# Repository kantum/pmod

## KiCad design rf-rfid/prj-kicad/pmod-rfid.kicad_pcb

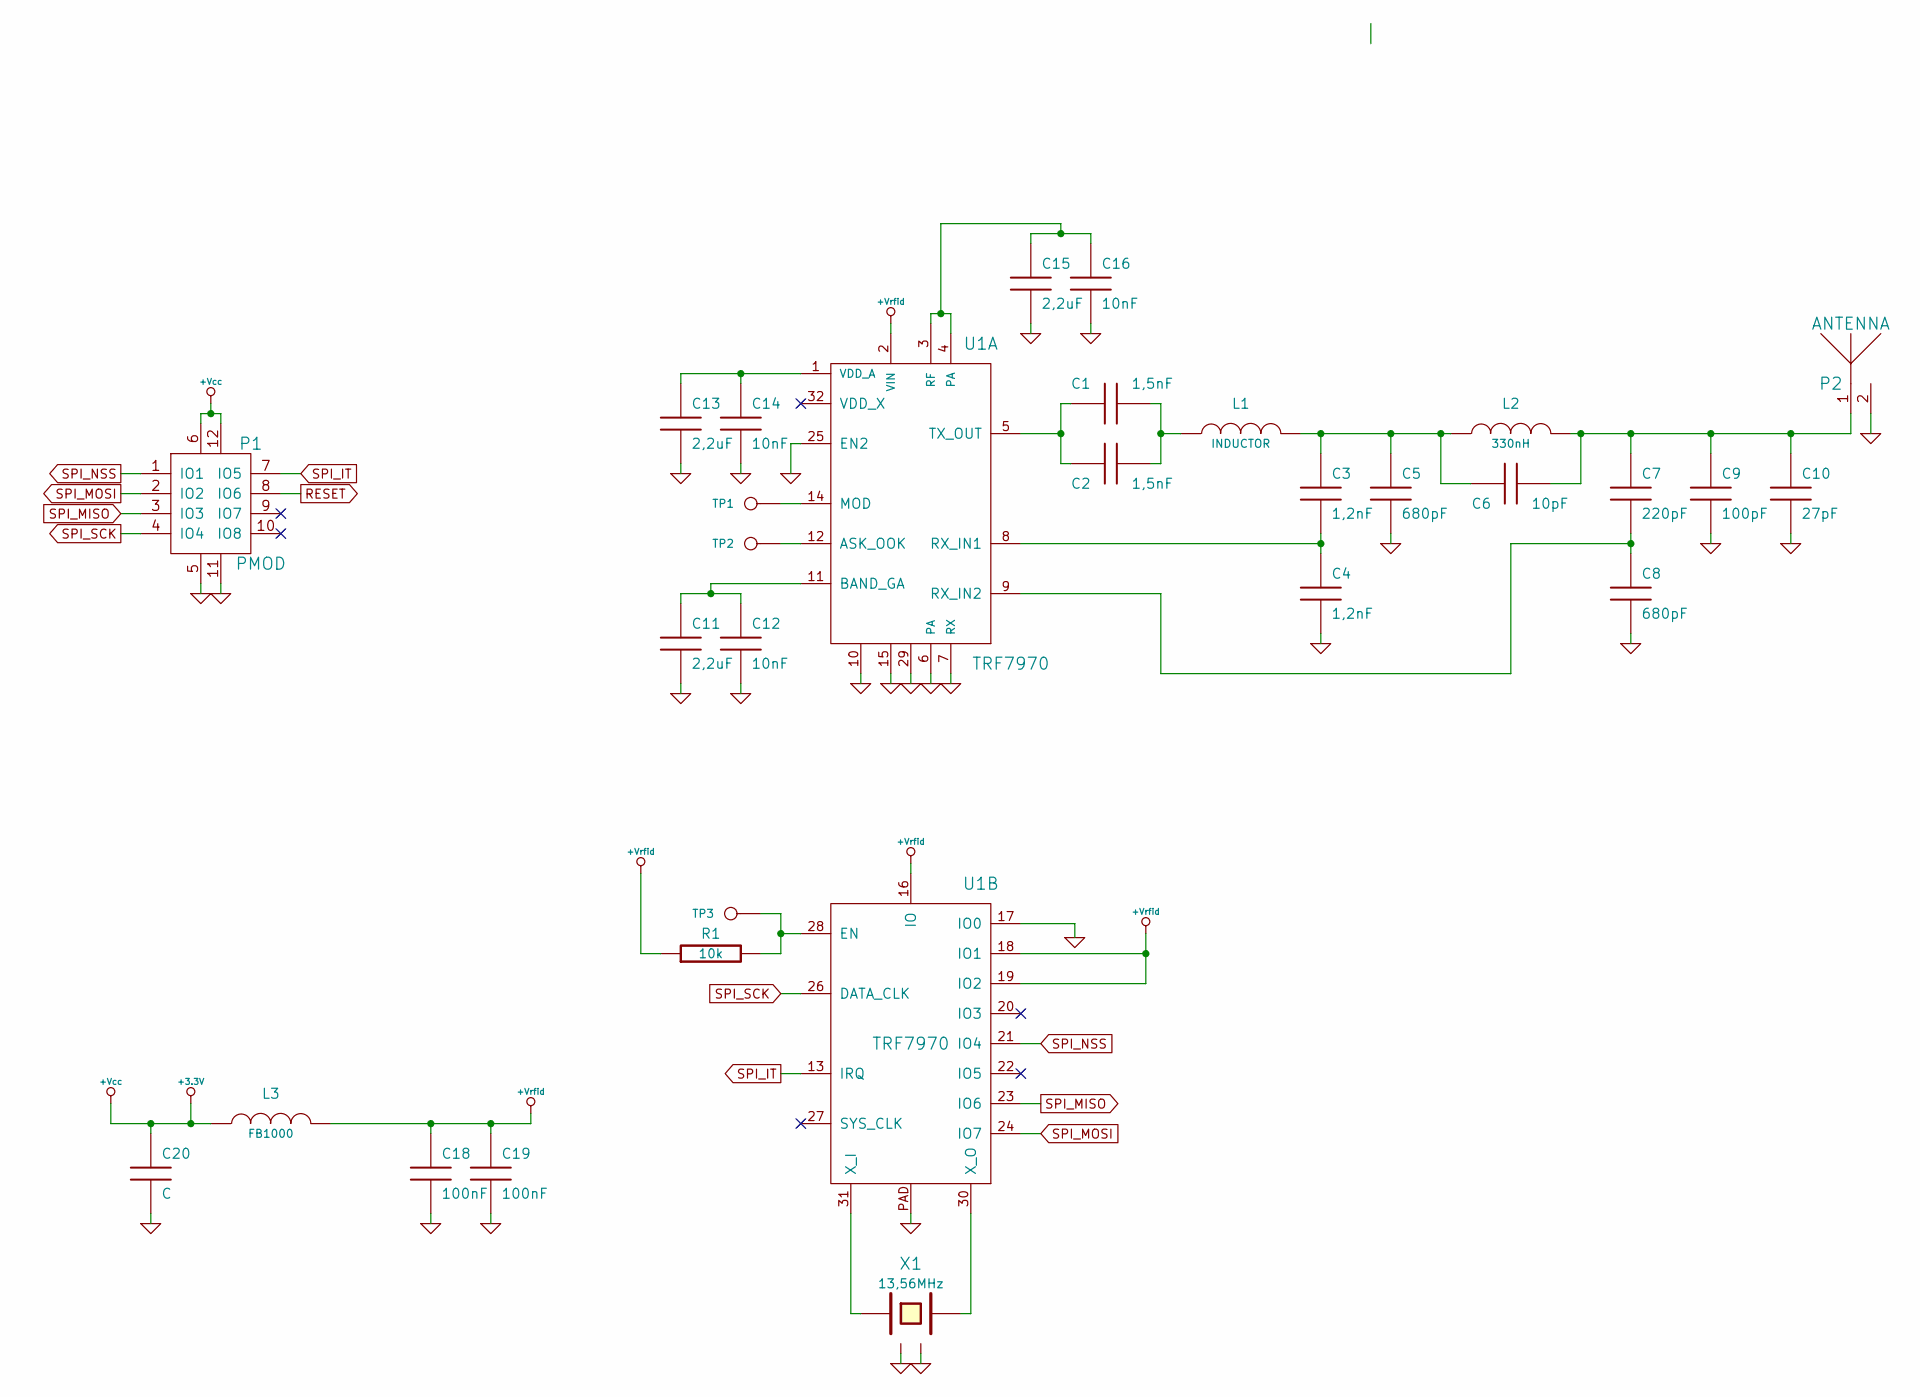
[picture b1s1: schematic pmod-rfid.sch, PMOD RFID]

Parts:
C1, C2: 1,5nF; SMD0603
C3, C4: 1,2nF; SMD0603
C5, C8: 680pF; SMD0603
C6: 10pF; SMD0603
C7: 220pF; SMD0603
C9: 100pF; SMD0603
C10: 27pF; SMD0603
C11, C13, C15: 2,2uF; SMD0603
C12, C14, C16: 10nF; SMD0603
C18, C19: 100nF; SMD0603
C20: C; SMD0805
L1: INDUCTOR; I_1008CS
L2: 330nH; I_1008CS
L3: FB1000; SMD0603
P1: PMOD; CONN_PMOD-Male
P2: ANTENNA; CONN_SMA_RA
R1: 10k; SMD0603
TP1, TP2, TP3: CONN_1; TP_SMD
U1: TRF7970; QFN32
X1: 13,56MHz; Q_SMD5x3

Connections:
+3.3V: C20.1, L3.1, P1.6, P1.12
+Vrfid: C18.1, C19.1, L3.2, R1.1, U1.2 (VIN), U1.16 (IO), U1.18 (IO1), U1.19 (IO2)
GND: C4.2, C5.2, C8.2, C9.2, C10.2, C11.2, C12.2, C13.2, C14.2, C15.2, C16.2, C18.2, C19.2, C20.2, P1.5, P1.11, P2.2, U1.6 (PA), U1.7 (RX), U1.10, U1.15, U1.17 (IO0), U1.25 (EN2), U1.29, U1.PAD, X1.2, X1.4
unnamed: C1.1, C2.1, L1.1
unnamed: C1.2, C2.2, U1.5 (TX_OUT)
unnamed: C3.1, C5.1, C6.2, L1.2, L2.1
unnamed: C3.2, C4.1, U1.8 (RX_IN1)
unnamed: C7.2, C8.1, U1.9 (RX_IN2)
unnamed: C6.1, C7.1, C9.1, C10.1, L2.2, P2.1
unnamed: C11.1, C12.1, U1.11 (BAND_GA)
unnamed: C13.1, C14.1, U1.1 (VDD_A)
unnamed: C15.1, C16.1, U1.3 (RF), U1.4 (PA)
unnamed: R1.2, TP3.1, U1.28 (EN)
unnamed: TP1.1, U1.14 (MOD)
unnamed: TP2.1, U1.12 (ASK_OOK)
unnamed: U1.30 (X_O), X1.3
unnamed: U1.31 (X_I), X1.1
RESET: P1.8 (IO6)
SPI_IT: P1.7 (IO5), U1.13 (IRQ)
SPI_MISO: P1.3 (IO3), U1.23 (IO6)
SPI_MOSI: P1.2 (IO2), U1.24 (IO7)
SPI_NSS: P1.1 (IO1), U1.21 (IO4)
SPI_SCK: P1.4 (IO4), U1.26 (DATA_CLK)

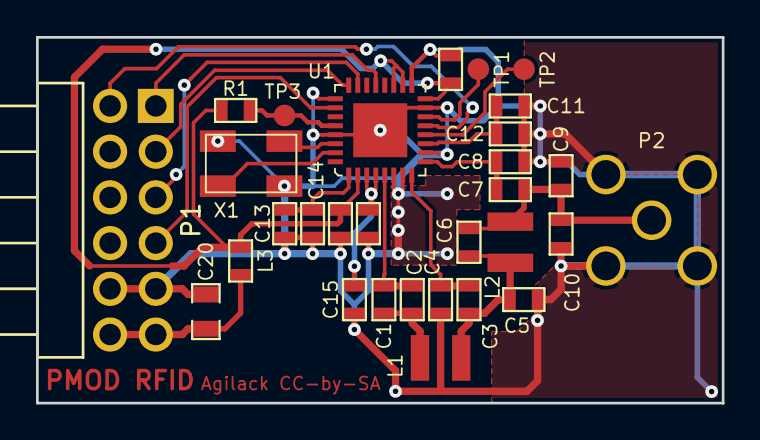
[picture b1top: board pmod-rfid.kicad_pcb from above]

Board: 2 copper layers, 38.1 x 20.3 mm, 30 parts (0 on the bottom side), 22 nets.

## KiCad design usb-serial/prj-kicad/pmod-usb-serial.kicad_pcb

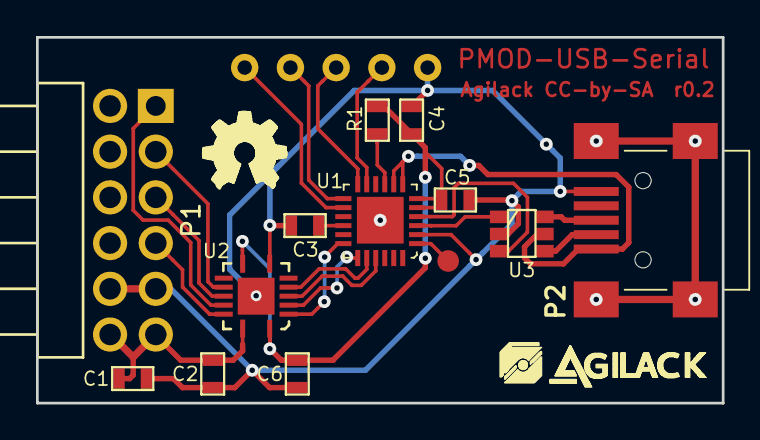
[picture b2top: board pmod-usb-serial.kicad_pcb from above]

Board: 2 copper layers, 38.1 x 20.3 mm, 20 parts (0 on the bottom side), 23 nets.

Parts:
C1, C4: 1uF; SMD0603
C2, C5, C6: 100nF; SMD0603
C3: 4,7uF; SMD0603
P1: PMOD; CONN_PMOD-Male
P2: CONN_MiniUSB-AB; CONN_65100516121
R1: 4,7k; SMD0603
TP1, TP2, TP3, TP4, TP5: CONN_1; TP_PIN
TP6: CONN_1; TP_SMD
U1: CP2104; QFN24
U2: TXS0104; QFN14
U3: USBLC6-2; SOT23-6
agilack-11.5: 450px; logo-agilack-11.5
logo_ohw: VAL**; logo-ohw

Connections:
CP21_CTS: U1.18, U2.2
CP21_RTS: U1.19, U2.3
CP21_RXD: U1.20, U2.5
CP21_TXD: U1.21, U2.4
GND: C1.2, C2.2, C3.2, C4.2, C5.2, C6.2, P1.5, P1.11, P2.5, TP5.1, U1.2, U1.PAD, U2.7, U2.PAD, U3.2
unnamed: C3.1, U1.16
unnamed: P2.1, U1.7, U1.8, U3.5
unnamed: P2.2, U3.4
unnamed: P2.3, U3.6
unnamed: TP1.1, U1.14
unnamed: TP2.1, U1.13
unnamed: TP3.1, U1.12
unnamed: TP4.1, U1.11
unnamed: TP6.1, U1.1
unnamed: U1.3, U3.1
unnamed: U1.4, U3.3
PMOD_CTS: P1.1, U2.12
PMOD_RTS: P1.4, U2.13
PMOD_RXD: P1.3, U2.11
PMOD_TXD: P1.2, U2.10
RST: R1.2, U1.9
VCC: C1.1, C2.1, P1.6, P1.12, U2.14
VCC_3V3: C4.1, C5.1, C6.1, R1.1, U1.5, U1.6, U2.1, U2.8

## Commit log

2019-02-28 added txs0104
2019-03-01 pmod-usb-serial wait for validation
2019-03-01 rf_rfid updated
2019-03-01 usb-serial schematics minor update
2019-03-01 clean usb-serial's sym-lib-table
2019-03-01 rf-rfid finished

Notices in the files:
rf-rfid/prj-kicad/pmod-rfid.kicad_pcb:
Agilack CC-by-SA
rf-rfid/prj-kicad/pmod-rfid.sch:
Creative Commons ShareAlike with Attribution (CC BY-SA 3.0)
